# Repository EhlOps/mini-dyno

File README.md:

# Mini Dyno

### Overview

The mini dyno (dynamometer) is a tool created to measure the torque and power output of an engine or motor. The mechanical portion of the dyno functions as a water brake. This design is suited for engines up to 4 horsepower and is mainly used to measure the output of small engines used in RC cars.

An ESP32-C3 microcontroller reads a load cell (via HX711 ADC) and a Hall effect RPM sensor, converts the readings to torque (Nm) and RPM, then streams them over WiFi to an iOS companion app. The app plots a traditional dyno graph — torque and power vs RPM — in real time.

---

## System Architecture

```
Engine ──── Water Brake ──── Load Cell ──── HX711 ────┐
                  │                                   ESP32-C3 ── WiFi AP ── iPhone
              Hall Sensor (4 magnets/rev) ─────────────┘
```

| Measurement | Sensor | Pin |
|---|---|---|
| Force (→ Torque) | HX711 load cell ADC | PD_SCK: GPIO 7, DOUT: GPIO 6 |
| RPM | Digital Hall effect | GPIO 10 |
| Ready indicator | LED | GPIO 5 |

**Torque arm:** 100 mm (load cell to shaft centre)
**Torque (Nm):** `Force (N) × 0.1 m`
**Power (hp):** `Torque (Nm) × RPM × 2π / 60 / 745.7`

---

## Repository Structure

```
mini-dyno/
├── firmware/   — ESP-IDF project for ESP32-C3
└── software/   — iOS companion app (Xcode / SwiftUI)
```

See the README in each subdirectory for build and usage instructions.

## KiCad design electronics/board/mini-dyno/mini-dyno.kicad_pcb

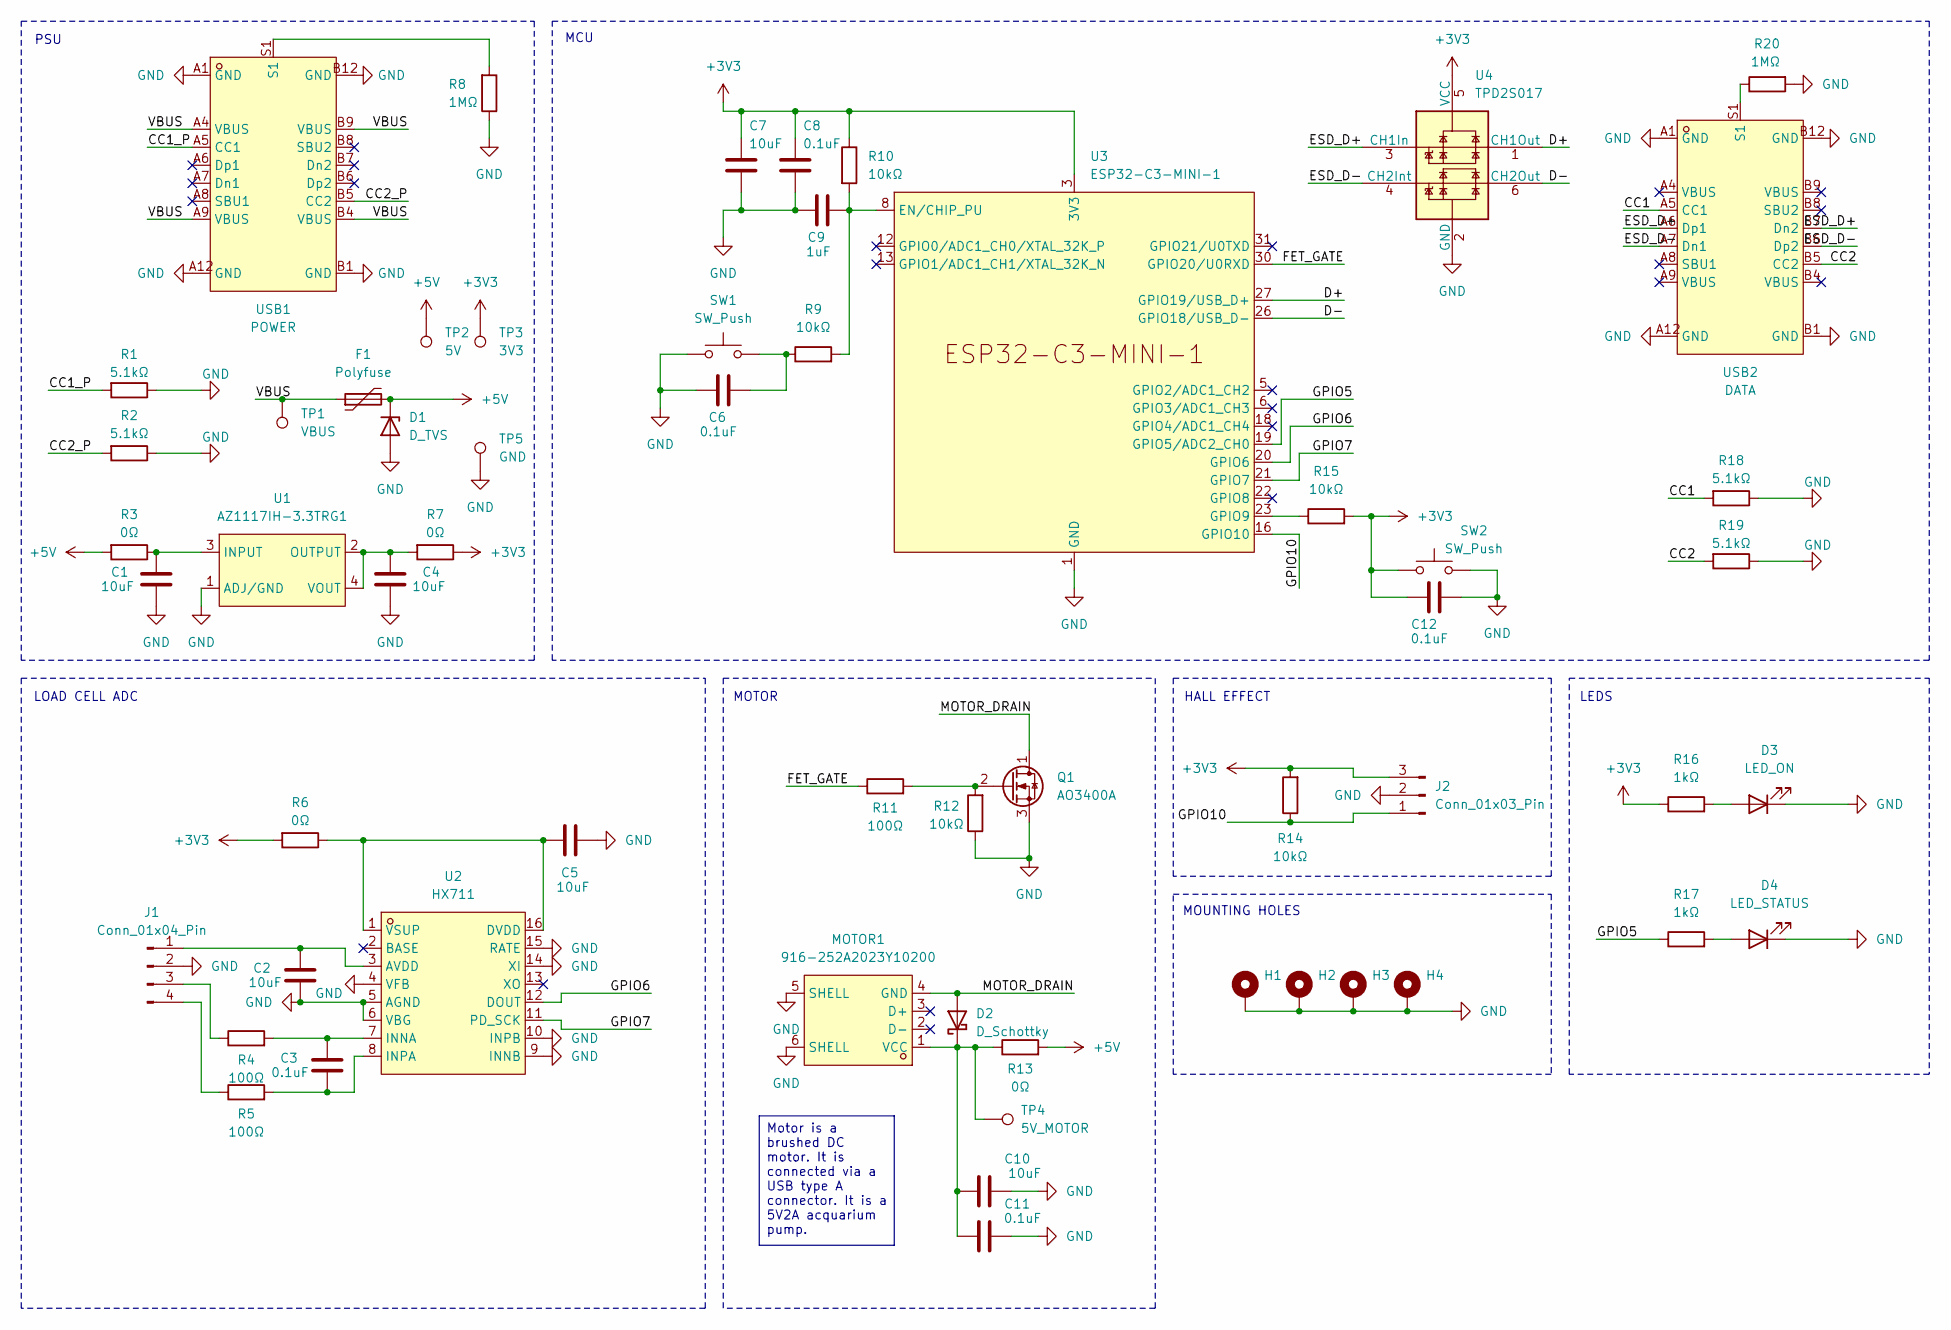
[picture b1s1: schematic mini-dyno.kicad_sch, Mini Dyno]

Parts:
C1, C2, C4, C5, C7, C10: 10uF; C_0805_2012Metric
C3, C6, C8, C11, C12: 0.1uF; C_0805_2012Metric
C9: 1uF; C_0805_2012Metric
D1: D_TVS; D_SMB
D2: D_Schottky; D_SMB
D3: LED_ON; LED_D5.0mm
D4: LED_STATUS; LED_D5.0mm
F1: Polyfuse; Fuse_0805_2012Metric_Pad1.15x1.40mm_HandSolder
H1, H2, H3, H4: MountingHole_3.2mm_M3_Pad
J1: Conn_01x04_Pin; PinHeader_1x04_P2.54mm_Horizontal
J2: Conn_01x03_Pin; PinHeader_1x03_P2.54mm_Horizontal
MOTOR1: 916-252A2023Y10200; USB-A-TH_916-352A102BY10200; LCSC Part C2763312
Q1: AO3400A; SOT-23_Handsoldering
R1, R2, R18, R19: 5.1kΩ; R_0805_2012Metric
R3, R6, R7, R13: 0Ω; R_1206_3216Metric_Pad1.30x1.75mm_HandSolder
R4, R5, R11: 100Ω; R_0805_2012Metric
R8, R20: 1MΩ; R_0805_2012Metric
R9, R10, R12, R14, R15: 10kΩ; R_0805_2012Metric
R16, R17: 1kΩ; R_0805_2012Metric
SW1, SW2: SW_Push; SW_Push_1P1T_NO_E-Switch_TL3301NxxxxxG
TP1: VBUS; TestPoint_THTPad_2.0x2.0mm_Drill1.0mm
TP2: 5V; TestPoint_THTPad_2.0x2.0mm_Drill1.0mm
TP3: 3V3; TestPoint_THTPad_2.0x2.0mm_Drill1.0mm
TP4: 5V_MOTOR; TestPoint_THTPad_2.0x2.0mm_Drill1.0mm
TP5: GND; TestPoint_THTPad_2.0x2.0mm_Drill1.0mm
U1: AZ1117IH-3.3TRG1; SOT-223-4_L6.5-W3.5-P2.30-LS7.0-BR; MPN AZ1117IH-3.3TRG1; LCSC Part C108495
U2: HX711; SOP-16_L10.0-W3.9-P1.27-LS6.0-BL; LCSC Part C6705483
U3: ESP32-C3-MINI-1
U4: TPD2S017; SOT-23-6
USB1: POWER; USC-C-SMD_USB4085-GF-A; MPN USB4085-GF-A; LCSC Part C7095263
USB2: DATA; USC-C-SMD_USB4085-GF-A; MPN USB4085-GF-A; LCSC Part C7095263

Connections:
+3V3: C7.1, C8.1, C12.1, J2.3, R6.2, R7.1, R10.1, R14.2, R15.2, R16.1, SW2.1, TP3.1 (1_1), U3.3 (3V3), U4.5 (VCC); also elsewhere on the board
+5V: D1.1 (K), F1.2, R3.2, R13.2, TP2.1 (1_1)
/CC1: R18.2, USB2.A5 (CC1)
/CC1_P: R1.2, USB1.A5 (CC1)
/CC2: R19.2, USB2.B5 (CC2)
/CC2_P: R2.2, USB1.B5 (CC2)
/D+: U3.27 (GPIO19/USB_D+), U4.1 (CH1Out)
/D-: U3.26 (GPIO18/USB_D-), U4.6 (CH2Out)
/ESD_D+: U4.3 (CH1In), USB2.A6 (Dp1), USB2.B7 (Dn2)
/ESD_D-: U4.4 (CH2Int), USB2.A7 (Dn1), USB2.B6 (Dp2)
/FET_GATE: R11.1, U3.30 (GPIO20/U0RXD)
/GPIO5: R17.1, U3.19 (GPIO5/ADC2_CH0)
/GPIO6: U2.12 (DOUT), U3.20 (GPIO6)
/GPIO7: U2.11 (PD_SCK), U3.21 (GPIO7)
/GPIO10: J2.1, R14.1, U3.16 (GPIO10)
/MOTOR_DRAIN: D2.2 (A), MOTOR1.4 (GND), Q1.1 (D)
/VBUS: F1.1, TP1.1 (1_1), USB1.A4 (VBUS), USB1.A9 (VBUS), USB1.B4 (VBUS), USB1.B9 (VBUS)
GND: C1.2, C2.1, C4.2, C5.1, C6.1, C7.2, C8.2, C9.1, C10.1, C11.1, C12.2, D1.2 (A), D3.1 (K), D4.1 (K), H1.1 (1_1), H2.1 (1_1), H3.1 (1_1), H4.1 (1_1), J1.2, J2.2, MOTOR1.5 (SHELL), MOTOR1.6 (SHELL), Q1.3 (S), R1.1, R2.1, R8.1, R12.1, R18.1, R19.1, R20.2, SW1.1, SW2.2, TP5.1 (1_1), U1.1 (ADJ/GND), U2.4 (VFB), U2.5 (AGND), U2.6 (VBG), U2.9 (INNB), U2.10 (INPB), U2.14 (XI), U2.15 (RATE), U3.1 (GND), U3.2 (GND), U3.11 (GND), U3.14 (GND), U3.36 (GND), U3.37 (GND), U3.38 (GND), U3.39 (GND), U3.40 (GND), U3.41 (GND), U3.42 (GND), U3.43 (GND), U3.44 (GND), U3.45 (GND), U3.46 (GND), U3.47 (GND), U3.48 (GND), U3.49 (GND), U3.50 (GND), U3.51 (GND), U3.52 (GND), U3.53 (GND), U4.2 (GND), USB1.A1 (GND), USB1.A12 (GND), USB1.B1 (GND), USB1.B12 (GND), USB2.A1 (GND), USB2.A12 (GND), USB2.B1 (GND), USB2.B12 (GND); also elsewhere on the board
unnamed 18: C6.2, R9.1, SW1.2; also elsewhere on the board
unnamed: C10.2, C11.2, D2.1 (K), MOTOR1.1 (VCC), R13.1, TP4.1 (1_1)
unnamed: D3.2 (A), R16.2
unnamed: D4.2 (A), R17.2
unnamed: C2.2, J1.1, U2.3 (AVDD)
unnamed: J1.3, R4.1
unnamed: J1.4, R5.1
unnamed: Q1.2 (G), R11.2, R12.2
unnamed: R8.2, USB1.S1
unnamed: R20.1, USB2.S1
unnamed: C1.1, R3.1, U1.3 (INPUT)
unnamed: C4.1, R7.2, U1.2 (OUTPUT), U1.4 (VOUT)
unnamed: C5.2, R6.1, U2.1 (VSUP), U2.16 (DVDD)
unnamed: C3.2, R4.2, U2.7 (INNA)
unnamed: C3.1, R5.2, U2.8 (INPA)
unnamed: C9.2, R9.2, R10.2, U3.8 (EN/CHIP_PU)
unnamed: R15.1, U3.23 (GPIO9)

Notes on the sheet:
PSU
HALL EFFECT
LEDS
MOUNTING HOLES
MCU
MOTOR
LOAD CELL ADC
Motor is a brushed DC motor. It is connected via a USB type A connector. It is a 5V2A acquarium pump.

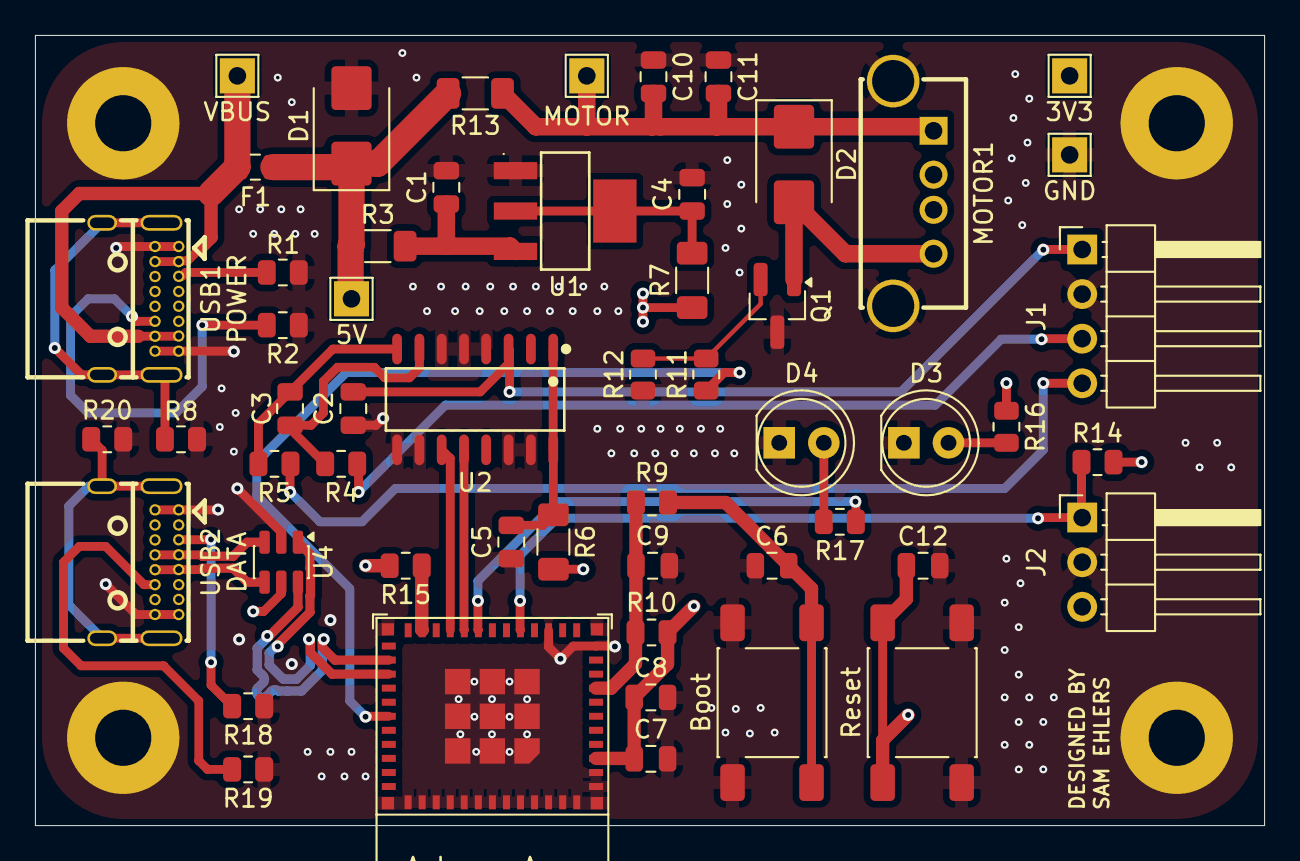
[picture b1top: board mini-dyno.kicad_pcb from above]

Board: 4 copper layers, 70.0 x 45.0 mm, 58 parts (0 on the bottom side), 35 nets.

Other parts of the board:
Boot: SW_Push; SW_Push_1P1T_NO_E-Switch_TL3301NxxxxxG
Reset: SW_Push; SW_Push_1P1T_NO_E-Switch_TL3301NxxxxxG

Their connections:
+3V3: Reset.1; also elsewhere on the board
GND: Boot.1, Reset.2; also elsewhere on the board
unnamed 18: Boot.2; also elsewhere on the board

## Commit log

2025-12-12 Init
2025-12-12 Add MIT License file
2025-12-12 Add CERN license
2025-12-13 Add firmware project
2026-02-04 Add FEA
2026-02-04 Add FEA:
2026-02-22 Completed board
2026-02-22 Update PCB
2026-02-23 Add solid parts
2026-03-13 Firmware
2026-03-13 Add software
2026-03-14 Add software and firmware functionality
2026-03-17 Update software and firmware
2026-06-04 Update PCB Layout
2026-06-05 Update Layout
2026-06-15 New Rust Firware
2026-06-18 Update Firmware
